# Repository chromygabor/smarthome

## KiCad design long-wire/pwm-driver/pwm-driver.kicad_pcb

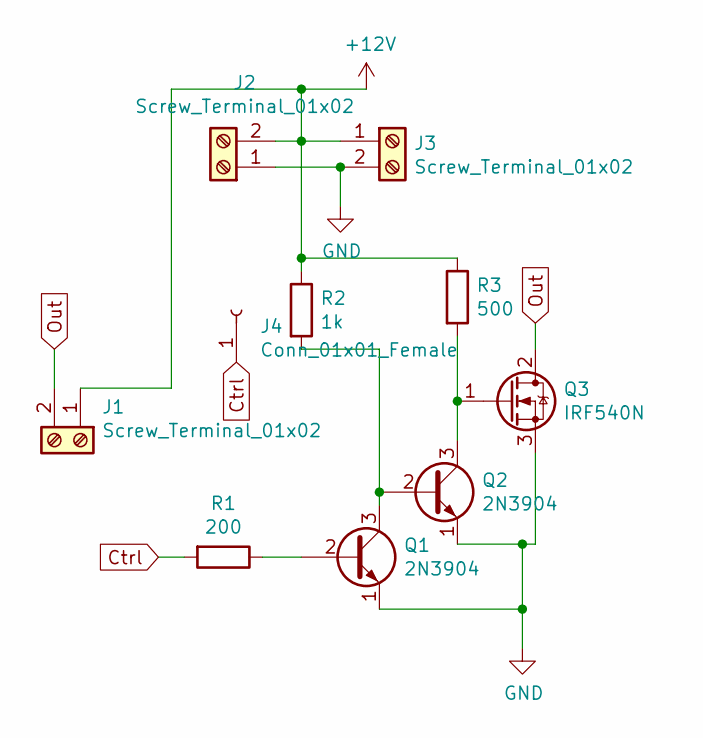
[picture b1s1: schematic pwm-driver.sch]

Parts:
J1, J2, J3: Screw_Terminal_01x02; TerminalBlock_bornier-2_P5.08mm
J4: Conn_01x01_Female; Pin_D0.7mm_L6.5mm_W1.8mm_FlatFork
Q1, Q2: 2N3904; TO-92_Inline
Q3: IRF540N; TO-220-3_Vertical
R1: 200; R_Axial_DIN0204_L3.6mm_D1.6mm_P5.08mm_Horizontal
R2: 1k; R_Axial_DIN0204_L3.6mm_D1.6mm_P5.08mm_Horizontal
R3: 500; R_Axial_DIN0204_L3.6mm_D1.6mm_P5.08mm_Horizontal

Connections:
+12V: J1.1, J2.2, J3.1, R2.1, R3.1
Ctrl: J4.1, R1.2
GND: J2.1, J3.2, Q1.1 (E), Q2.1 (E), Q3.3 (S)
unnamed: Q1.2 (B), R1.1
unnamed: Q1.3 (C), Q2.2 (B), R2.2
unnamed: Q2.3 (C), Q3.1 (G), R3.2
Out: J1.2, Q3.2 (D)

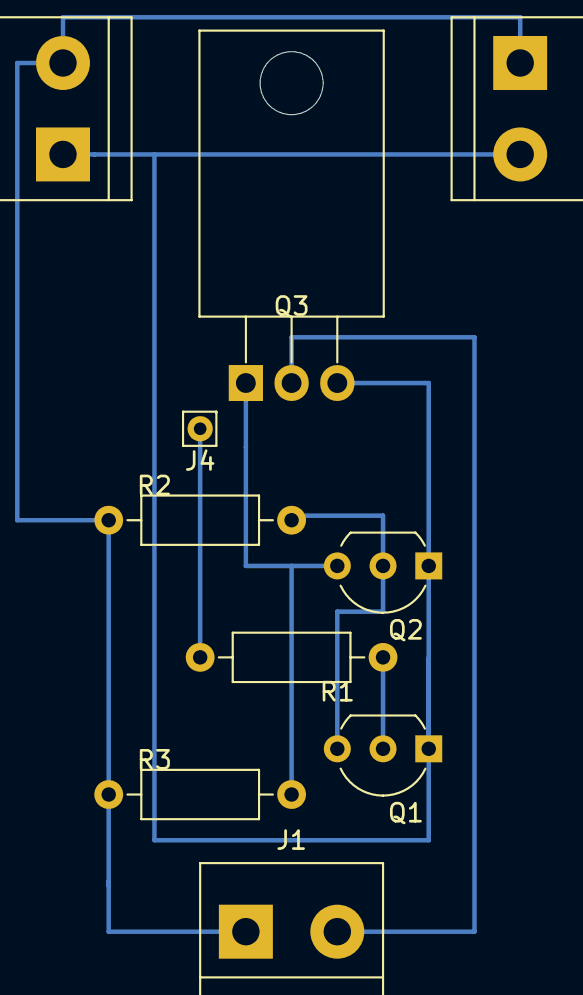
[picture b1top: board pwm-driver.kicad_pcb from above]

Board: 2 copper layers, 10 parts (0 on the bottom side), 7 nets.

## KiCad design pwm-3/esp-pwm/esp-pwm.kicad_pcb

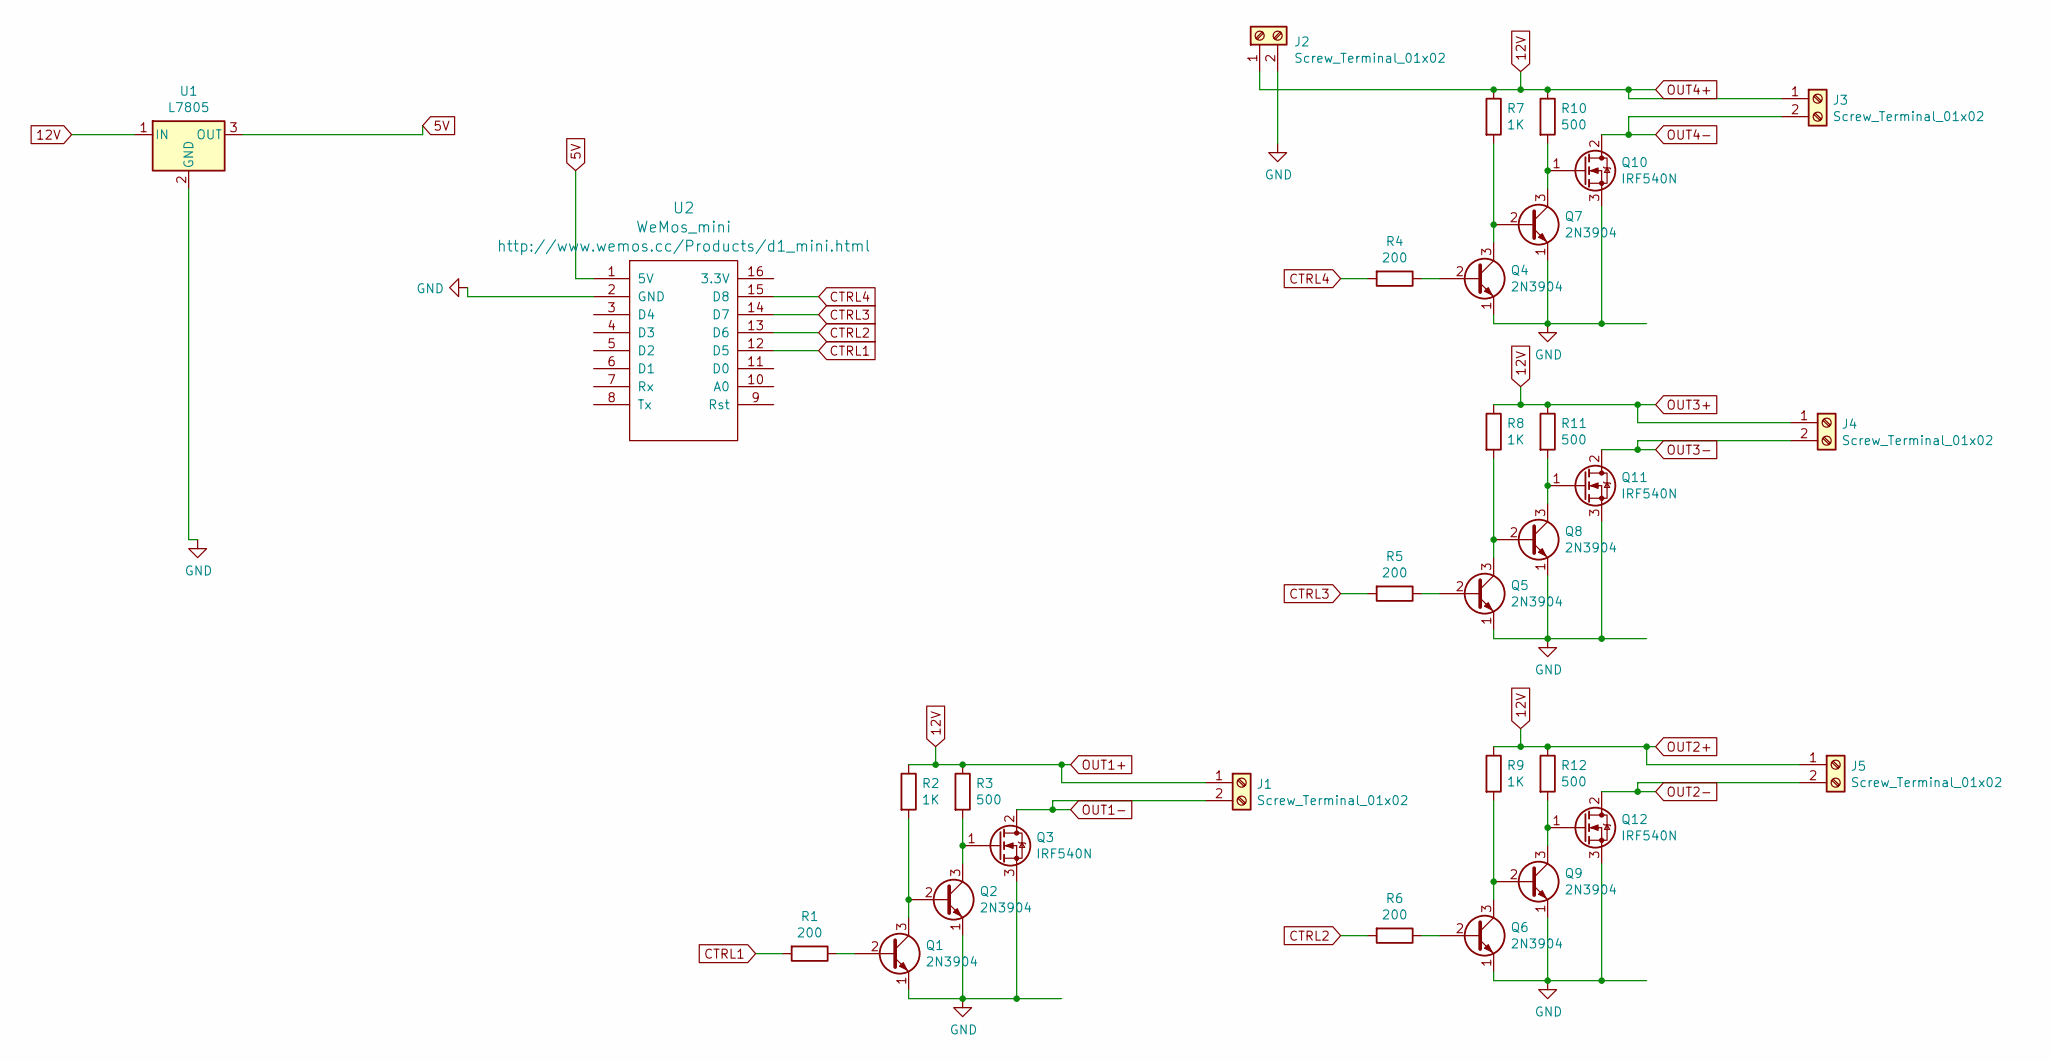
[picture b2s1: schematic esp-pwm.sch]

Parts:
J1, J2, J3, J4, J5: Screw_Terminal_01x02; TerminalBlock_bornier-2_P5.08mm
Q1, Q2, Q4, Q5, Q6, Q7, Q8, Q9: 2N3904; TO-92
Q3, Q10, Q11, Q12: IRF540N; TO-220-3_Vertical
R1, R4, R5, R6: 200; R_Axial_DIN0516_L15.5mm_D5.0mm_P20.32mm_Horizontal
R2, R7, R8, R9: 1K; R_Axial_DIN0516_L15.5mm_D5.0mm_P20.32mm_Horizontal
R3, R10, R11, R12: 500; R_Axial_DIN0516_L15.5mm_D5.0mm_P20.32mm_Horizontal
U1: L7805; TO-220-3_Vertical
U2: WeMos_mini; D1_mini_board

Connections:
5V: U1.3 (OUT), U2.1 (5V)
12V: J1.1, J2.1, J3.1, J4.1, J5.1, R2.1, R3.1, R7.1, R8.1, R9.1, R10.1, R11.1, R12.1, U1.1 (IN)
CTRL1: R1.2, U2.12 (D5)
CTRL2: R6.2, U2.13 (D6)
CTRL3: R5.2, U2.14 (D7)
CTRL4: R4.2, U2.15 (D8)
GND: J2.2, Q1.1 (E), Q2.1 (E), Q3.3 (S), Q4.1 (E), Q5.1 (E), Q6.1 (E), Q7.1 (E), Q8.1 (E), Q9.1 (E), Q10.3 (S), Q11.3 (S), Q12.3 (S), U1.2 (GND), U2.2 (GND)
unnamed: Q1.2 (B), R1.1
unnamed: Q1.3 (C), Q2.2 (B), R2.2
unnamed: Q2.3 (C), Q3.1 (G), R3.2
unnamed: Q4.2 (B), R4.1
unnamed: Q4.3 (C), Q7.2 (B), R7.2
unnamed: Q5.2 (B), R5.1
unnamed: Q5.3 (C), Q8.2 (B), R8.2
unnamed: Q6.2 (B), R6.1
unnamed: Q6.3 (C), Q9.2 (B), R9.2
unnamed: Q7.3 (C), Q10.1 (G), R10.2
unnamed: Q8.3 (C), Q11.1 (G), R11.2
unnamed: Q9.3 (C), Q12.1 (G), R12.2
OUT1-: J1.2, Q3.2 (D)
OUT2-: J5.2, Q12.2 (D)
OUT3-: J4.2, Q11.2 (D)
OUT4-: J3.2, Q10.2 (D)

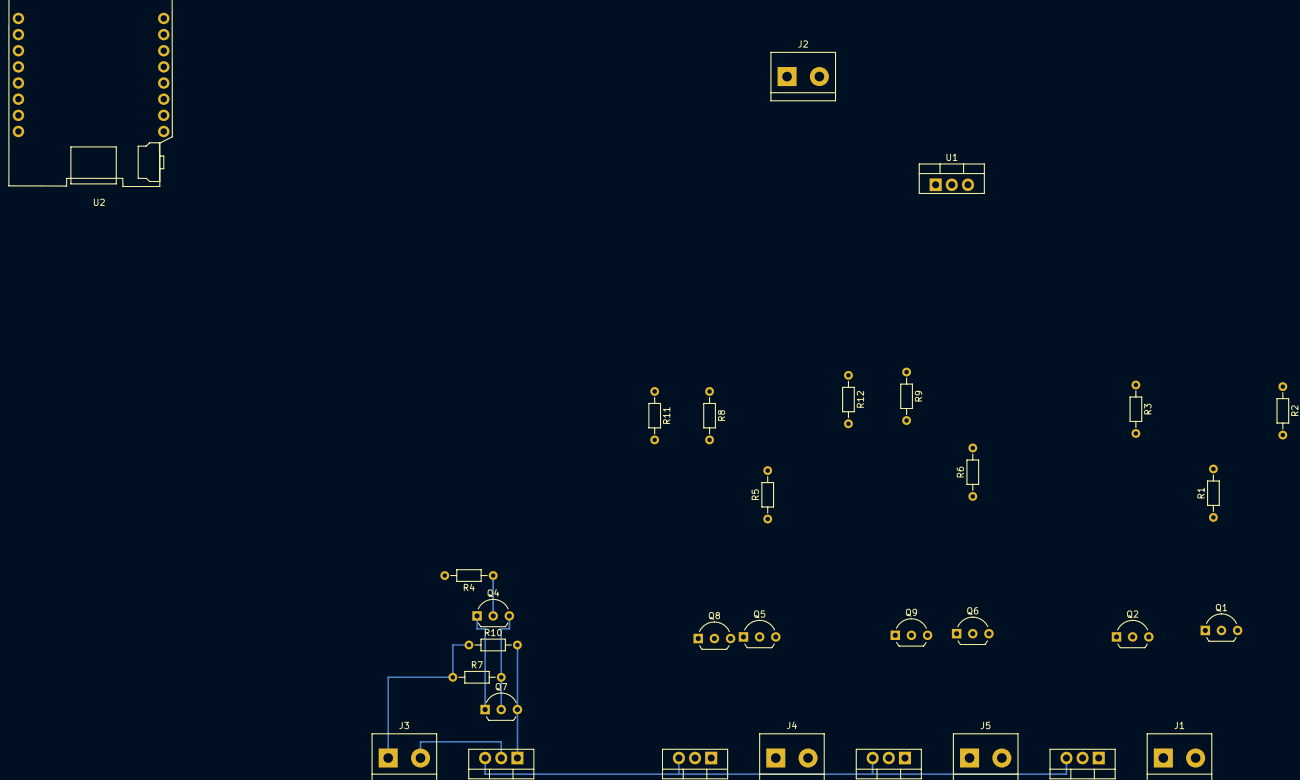
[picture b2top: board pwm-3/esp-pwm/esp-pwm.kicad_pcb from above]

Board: 2 copper layers, 31 parts (0 on the bottom side), 23 nets.

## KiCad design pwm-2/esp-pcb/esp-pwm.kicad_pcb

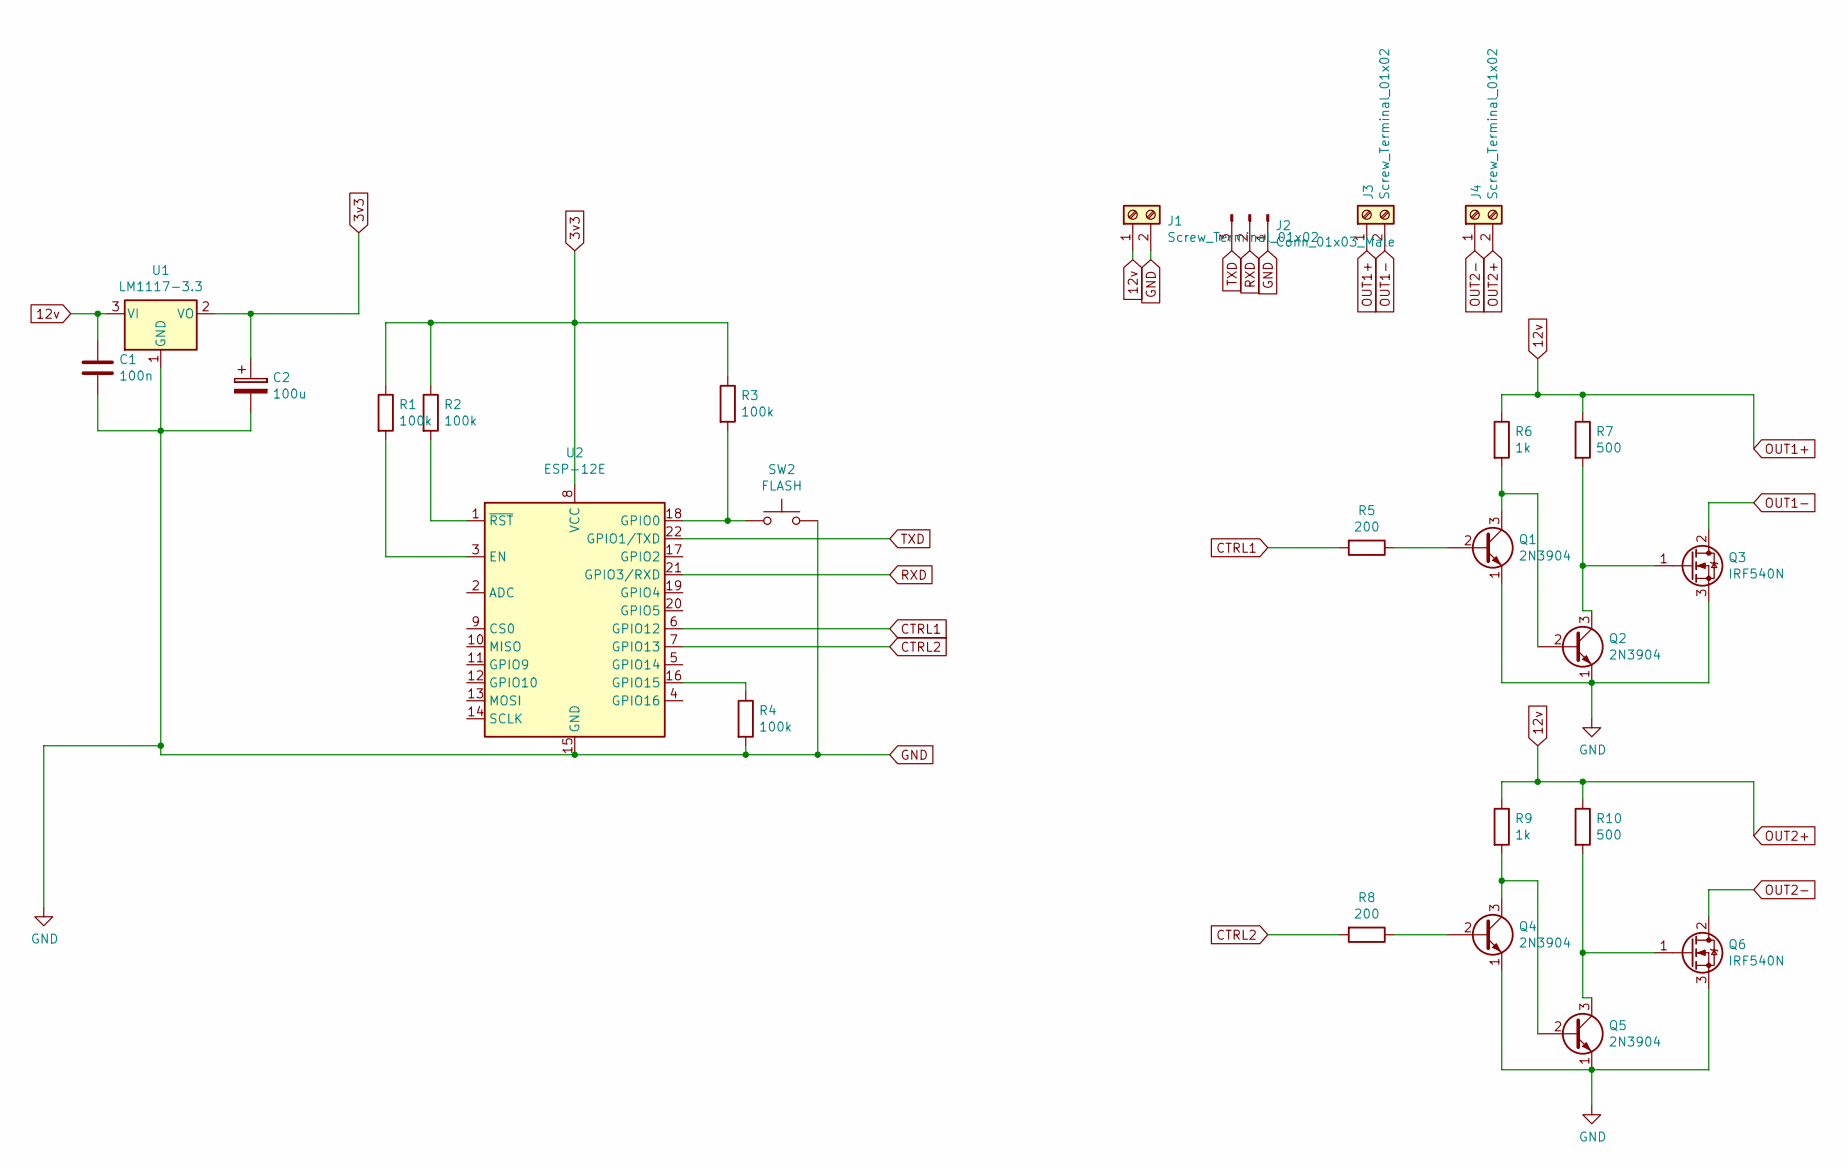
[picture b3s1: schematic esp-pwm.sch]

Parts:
C1: 100n; C_Disc_D7.5mm_W2.5mm_P5.00mm
C2: 100u; CP_Radial_D5.0mm_P2.50mm
J1, J3, J4: Screw_Terminal_01x02; TerminalBlock_bornier-2_P5.08mm
J2: Conn_01x03_Male; PinHeader_1x03_P2.54mm_Horizontal
Q1, Q2, Q4, Q5: 2N3904; TO-92_Inline_Wide
Q3, Q6: IRF540N; TO-220-3_Vertical
R1, R2, R3: 100k; R_Axial_DIN0207_L6.3mm_D2.5mm_P2.54mm_Vertical
R4: 100k; R_Axial_DIN0207_L6.3mm_D2.5mm_P7.62mm_Horizontal
R5, R8: 200; R_Axial_DIN0204_L3.6mm_D1.6mm_P7.62mm_Horizontal
R6, R9: 1k; R_Axial_DIN0204_L3.6mm_D1.6mm_P7.62mm_Horizontal
R7, R10: 500; R_Axial_DIN0204_L3.6mm_D1.6mm_P7.62mm_Horizontal
SW2: FLASH; SW_PUSH_6mm_H5mm
U1: LM1117-3.3; TO-220-3_Vertical
U2: ESP-12E

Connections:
3v3: C2.1, R1.1, R2.1, R3.1, U1.2 (VO), U2.8 (VCC)
12v: C1.1, J1.1, J3.1, J4.2, R6.1, R7.1, R9.1, R10.1, U1.3 (VI)
CTRL1: R5.2, U2.6 (GPIO12)
CTRL2: R8.2, U2.7 (GPIO13)
GND: C1.2, C2.2, J1.2, J2.1, Q1.1 (E), Q2.1 (E), Q3.3 (S), Q4.1 (E), Q5.1 (E), Q6.3 (S), R4.2, SW2.2, U1.1 (GND), U2.15 (GND)
unnamed: Q1.2 (B), R5.1
unnamed: Q1.3 (C), Q2.2 (B), R6.2
unnamed: Q2.3 (C), Q3.1 (G), R7.2
unnamed: Q4.2 (B), R8.1
unnamed: Q4.3 (C), Q5.2 (B), R9.2
unnamed: Q5.3 (C), Q6.1 (G), R10.2
unnamed: R1.2, U2.3 (EN)
unnamed: R2.2, U2.1 (~RST)
unnamed: R3.2, SW2.1, U2.18 (GPIO0)
unnamed: R4.1, U2.16 (GPIO15)
OUT1-: J3.2, Q3.2 (D)
OUT2-: J4.1, Q6.2 (D)
RXD: J2.2, U2.21 (GPIO3/RXD)
TXD: J2.3, U2.22 (GPIO1/TXD)

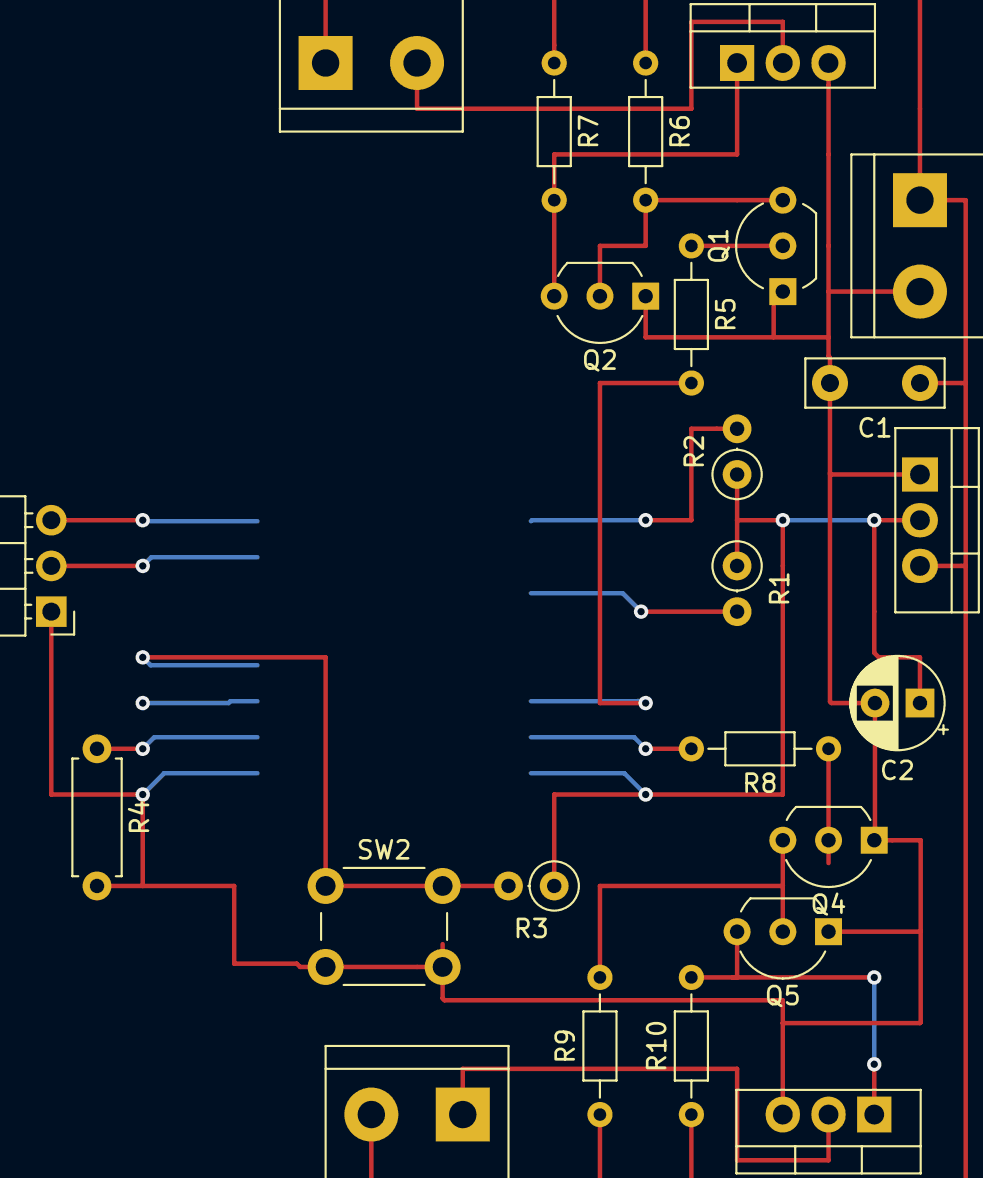
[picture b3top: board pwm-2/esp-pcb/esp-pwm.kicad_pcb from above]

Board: 2 copper layers, 25 parts (1 on the bottom side), 19 nets.

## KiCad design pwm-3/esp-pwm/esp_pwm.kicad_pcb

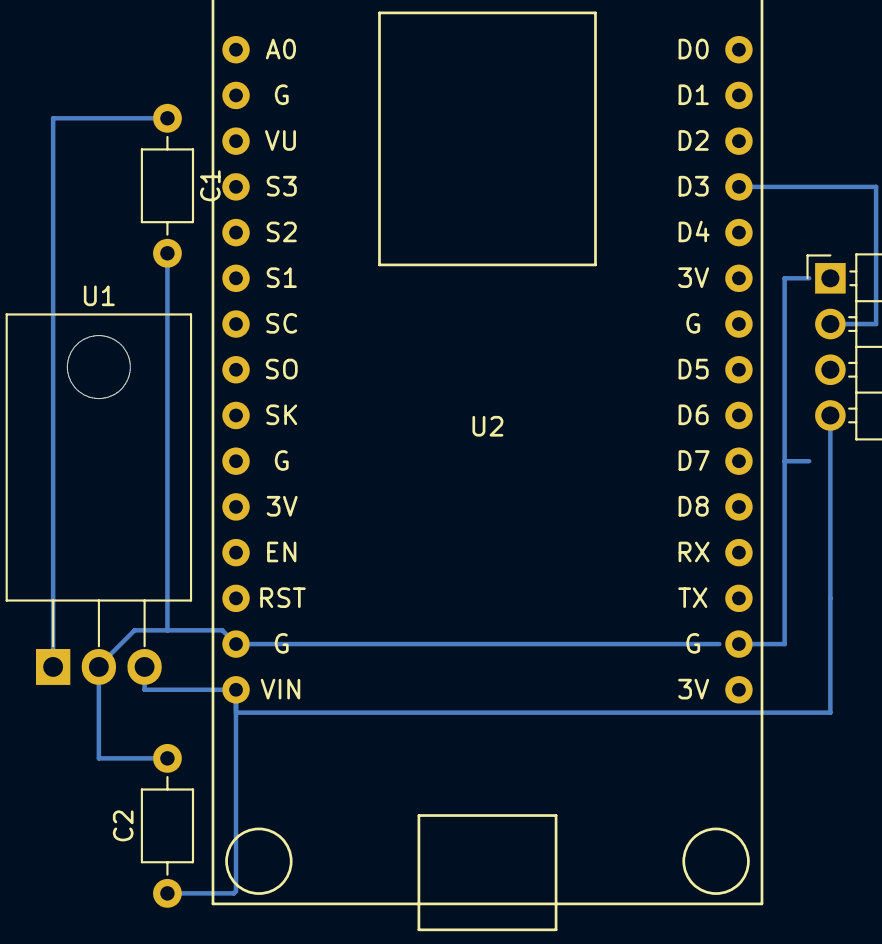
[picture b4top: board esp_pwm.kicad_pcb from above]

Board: 2 copper layers, 5 parts (0 on the bottom side), 4 nets.

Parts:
C1, C2: 100n; C_Axial_L3.8mm_D2.6mm_P7.50mm_Horizontal
J6: Screw_Terminal_01x04; PinHeader_1x04_P2.54mm_Horizontal
U1: L7805; TO-220-3_Horizontal_TabDown
U2: NodeMCU1.0(ESP-12E); NodeMCU1.0(12-E)

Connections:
5v: C2.1, J6.4, U1.3, U2.15
12v: C1.1, U1.1
GND: C1.2, C2.2, J6.1, U1.2, U2.14
Radio: J6.2, U2.27

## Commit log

2019-01-07 Created PWM2
2019-01-13 PWM2
2019-01-20 Added rf-receiver
2019-02-01 home-assistant playground
2019-11-12 PWM-3
